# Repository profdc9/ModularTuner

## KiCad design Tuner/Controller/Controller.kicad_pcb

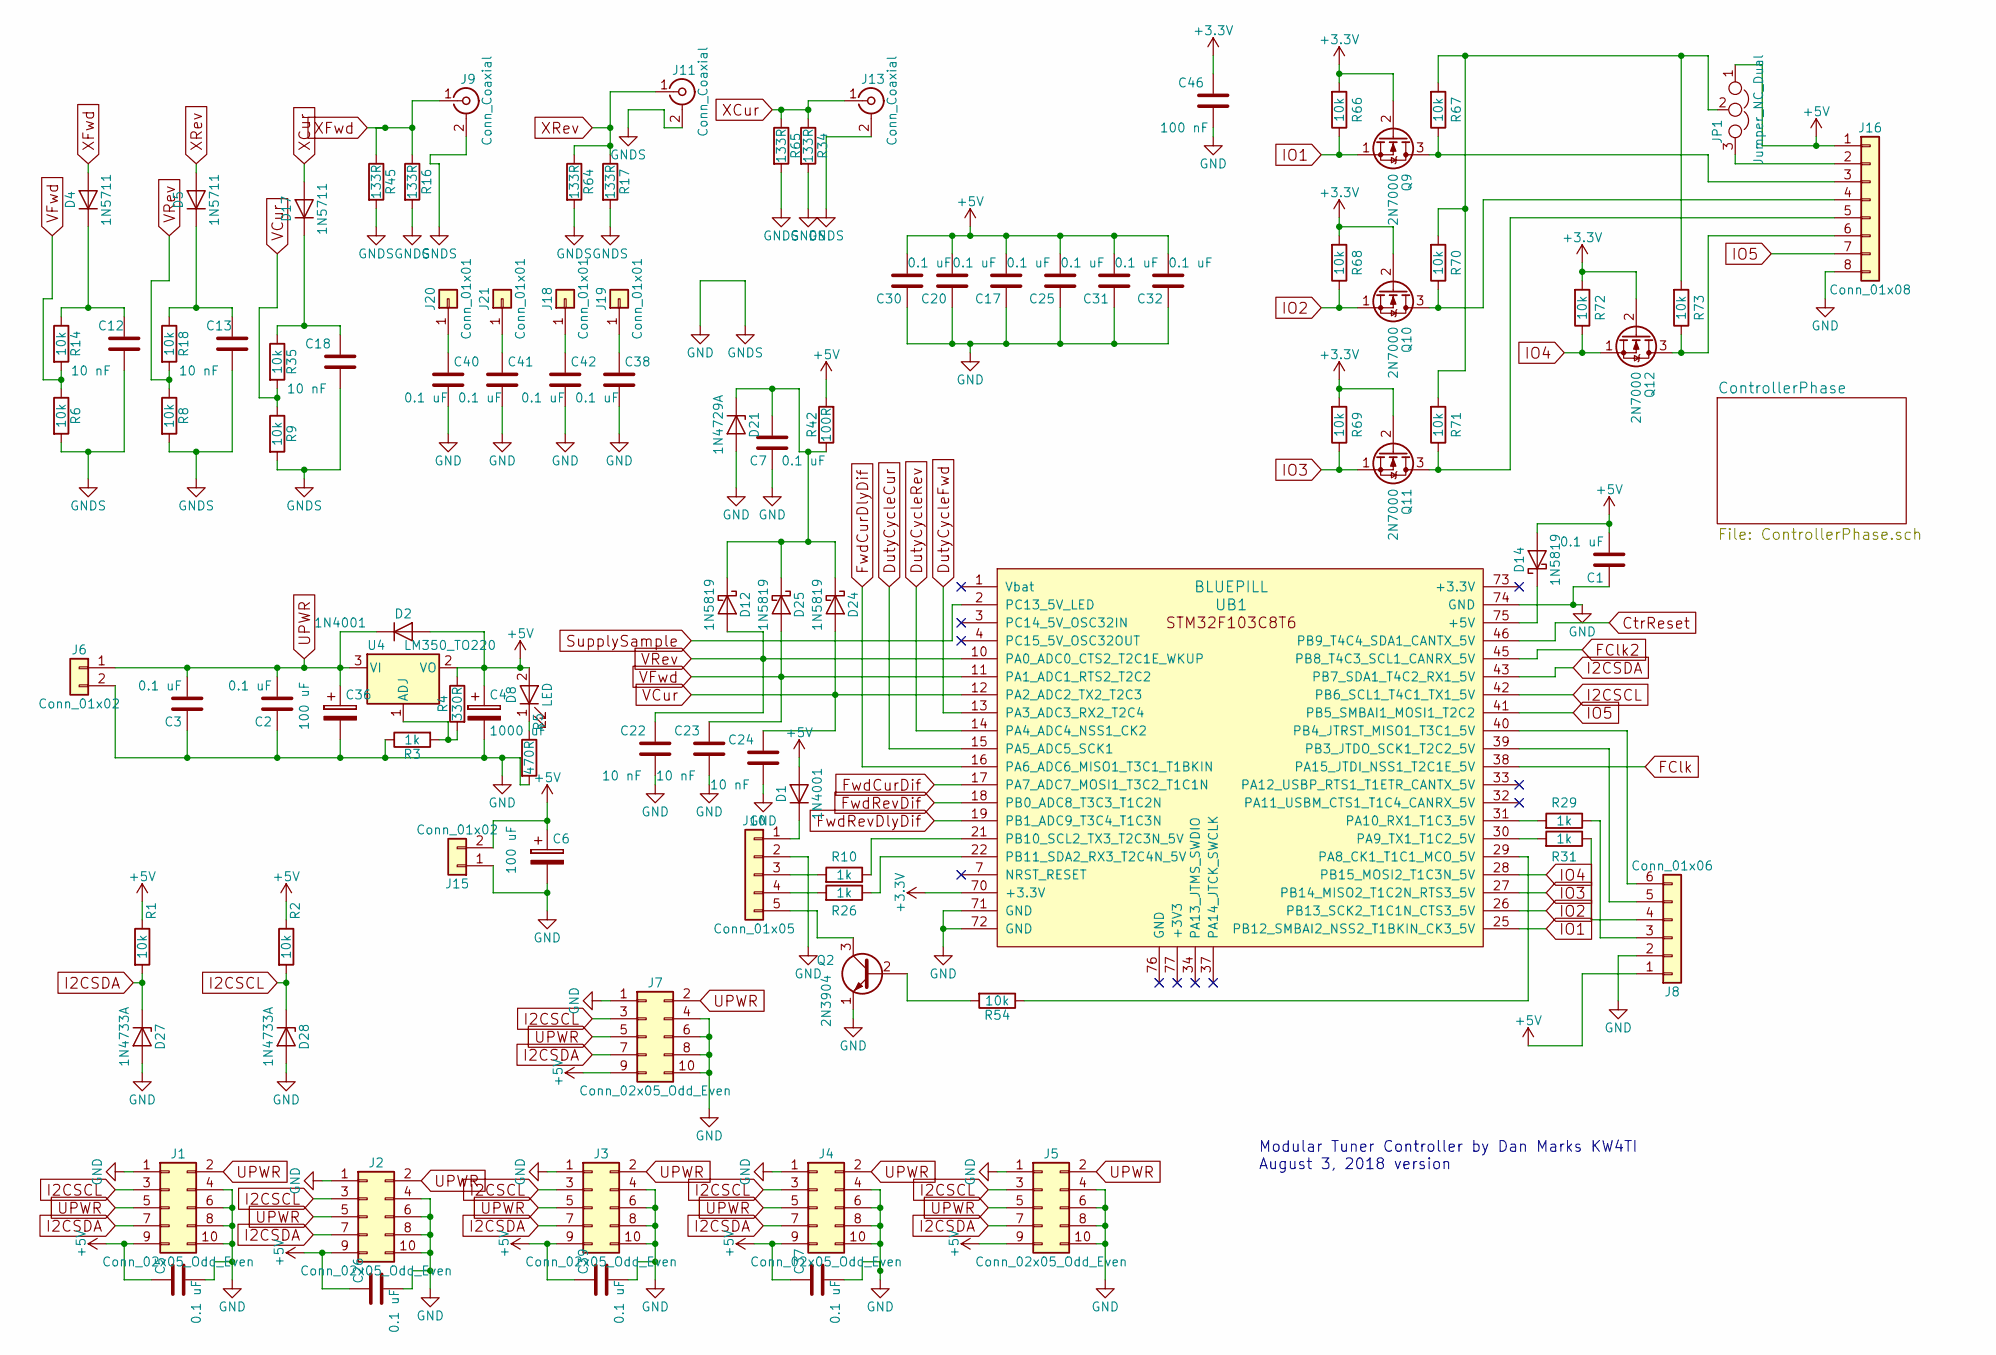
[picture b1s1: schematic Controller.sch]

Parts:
C1, C2, C7: 0.1 uF; C_Disc_D5.0mm_W2.5mm_P5.00mm
C3, C5, C17, C20, C25, C26, C30, C31, C32, C37, C38, C39, C40, C41, C42: 0.1 uF; C_Disc_D5.0mm_W2.5mm_P2.50mm
C4: 1000 uF; CP_Radial_D10.0mm_P5.00mm
C6, C36: 100 uF; CP_Radial_D5.0mm_P2.50mm
C12, C13, C18: 10 nF; C_Disc_D5.0mm_W2.5mm_P2.50mm
C22, C23, C24: 10 nF; C_Disc_D5.0mm_W2.5mm_P5.00mm
C46: 100 nF; C_Disc_D5.0mm_W2.5mm_P2.50mm
D1, D2: 1N4001; D_DO-41_SOD81_P7.62mm_Horizontal
D4, D5, D17: 1N5711; D_DO-35_SOD27_P7.62mm_Horizontal
D8: LED; LED_D3.0mm
D12, D14, D24, D25: 1N5819; D_DO-41_SOD81_P7.62mm_Horizontal
D21: 1N4729A; D_DO-41_SOD81_P7.62mm_Horizontal
D27, D28: 1N4733A; D_DO-41_SOD81_P7.62mm_Horizontal
J1, J2, J3, J4, J5, J7: Conn_02x05_Odd_Even; Pin_Header_Straight_2x05_Pitch2.54mm
J6, J15: Conn_01x02; TerminalBlock_bornier-2_P5.08mm
J8: Conn_01x06; Pin_Header_Straight_1x06_Pitch2.54mm
J9, J11, J13: Conn_Coaxial; bnc_90_1-1337543-0_pad_combo
J10: Conn_01x05; Pin_Header_Straight_1x05_Pitch2.54mm
J16: Conn_01x08; Pin_Header_Straight_1x08_Pitch2.54mm
J18, J19, J20, J21: Conn_01x01; 1pin
JP1: Jumper_NC_Dual; Pin_Header_Straight_1x03_Pitch2.54mm
Q2: 2N3904; TO-92_Molded_Narrow
Q9, Q10, Q11, Q12: 2N7000; TO-92_Molded_Narrow
R1, R2, R6, R8, R9, R14, R18, R35, R54, R66, R67, R68, R69, R70, R71, R72, R73: 10k; R_Axial_DIN0207_L6.3mm_D2.5mm_P7.62mm_Horizontal
R3, R10, R26, R29, R31: 1k; R_Axial_DIN0207_L6.3mm_D2.5mm_P7.62mm_Horizontal
R4: 330R; R_Axial_DIN0207_L6.3mm_D2.5mm_P7.62mm_Horizontal
R5: 470R; R_Axial_DIN0207_L6.3mm_D2.5mm_P7.62mm_Horizontal
R16, R17, R34, R45, R64, R65: 133R; R_Axial_DIN0309_L9.0mm_D3.2mm_P12.70mm_Horizontal
R42: 100R; R_Axial_DIN0207_L6.3mm_D2.5mm_P7.62mm_Horizontal
U4: LM350_TO220; TO-220-3_Vertical
UB1: BLUEPILL

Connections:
+3V3: C46.1, Q9.2 (G), Q10.2 (G), Q11.2 (G), Q12.2 (G), R66.2, R68.2, R69.2, R72.2, UB1.70 (+3.3V)
CtrReset: UB1.46 (PB9_T4C4_SDA1_CANTX_5V); also elsewhere on the board
DutyCycleCur: UB1.15 (PA5_ADC5_SCK1); also elsewhere on the board
DutyCycleFwd: UB1.13 (PA3_ADC3_RX2_T2C4); also elsewhere on the board
DutyCycleRev: UB1.14 (PA4_ADC4_NSS1_CK2); also elsewhere on the board
FClk2: UB1.45 (PB8_T4C3_SCL1_CANRX_5V); also elsewhere on the board
FwdCurDif: UB1.17 (PA7_ADC7_MOSI1_T3C2_T1C1N); also elsewhere on the board
FwdCurDlyDif: UB1.16 (PA6_ADC6_MISO1_T3C1_T1BKIN); also elsewhere on the board
FwdRevDif: UB1.18 (PB0_ADC8_T3C3_T1C2N); also elsewhere on the board
FwdRevDlyDif: UB1.19 (PB1_ADC9_T3C4_T1C3N); also elsewhere on the board
GND: C1.1, C2.1, C3.1, C4.2, C5.2, C6.2, C7.1, C12.2, C13.2, C17.1, C18.2, C20.1, C22.2, C23.2, C24.2, C25.1, C26.2, C30.1, C31.1, C32.1, C36.2, C37.2, C38.2, C39.2, C40.2, C41.2, C42.2, C46.2, D21.2 (A), D27.2 (A), D28.2 (A), J1.1, J1.4, J1.6, J1.8, J1.10, J2.1, J2.4, J2.6, J2.8, J2.10, J3.1, J3.4, J3.6, J3.8, J3.10, J4.1, J4.4, J4.6, J4.8, J4.10, J5.1, J5.4, J5.6, J5.8, J5.10, J6.2, J7.1, J7.4, J7.6, J7.8, J7.10, J8.2, J9.2 (Ext), J10.2, J11.2 (Ext), J13.2 (Ext), J15.1, J16.8, Q2.1 (E), R3.1, R5.2, R6.2, R8.2, R9.2, R16.2, R17.2, R34.2, R45.2, R64.2, R65.2, UB1.71 (GND), UB1.72 (GND), UB1.74 (GND); also elsewhere on the board
I2CSCL: D28.1 (K), J1.3, J2.3, J3.3, J4.3, J5.3, J7.3, R2.2, UB1.42 (PB6_SCL1_T4C1_TX1_5V)
I2CSDA: D27.1 (K), J1.7, J2.7, J3.7, J4.7, J5.7, J7.7, R1.2, UB1.43 (PB7_SDA1_T4C2_RX1_5V)
IO1: Q9.1 (S), R66.1, UB1.25 (PB12_SMBAI2_NSS2_T1BKIN_CK3_5V)
IO2: Q10.1 (S), R68.1, UB1.26 (PB13_SCK2_T1C1N_CTS3_5V)
IO3: Q11.1 (S), R69.1, UB1.27 (PB14_MISO2_T1C2N_RTS3_5V)
IO4: Q12.1 (S), R72.1, UB1.28 (PB15_MOSI2_T1C3N_5V)
IO5: J16.7, UB1.41 (PB5_SMBAI1_MOSI1_T2C2)
unnamed: C7.2, D12.1 (K), D21.1 (K), D24.1 (K), D25.1 (K), R42.1
unnamed: C12.1, D4.1 (K), R14.1
unnamed: C13.1, D5.1 (K), R18.1
unnamed: C18.1, D17.1 (K), R35.1
unnamed: C38.1, J19.1
unnamed: C40.1, J20.1
unnamed: C41.1, J21.1
unnamed: C42.1, J18.1
unnamed: D1.1 (K), J10.1
unnamed: D8.1 (K), R5.1
unnamed: D14.1 (K), UB1.75 (+5V)
unnamed: J8.3, R29.1
unnamed: J8.4, R31.1
unnamed: J8.5, UB1.39 (PB3_JTDO_SCK1_T2C2_5V)
unnamed: J8.6, UB1.40 (PB4_JTRST_MISO1_T3C1_5V)
unnamed: J10.3, R10.2
unnamed: J10.4, R26.2
unnamed: J10.5, Q2.3 (C)
unnamed: J16.2, JP1.3
unnamed: J16.3, Q9.3 (D), R67.1
unnamed: J16.4, Q10.3 (D), R70.1
unnamed: J16.5, Q11.3 (D), R71.1
unnamed: J16.6, Q12.3 (D), R73.1
unnamed: JP1.2, R67.2, R70.2, R71.2, R73.2
unnamed: Q2.2 (B), R54.2
unnamed: R3.2, R4.2, U4.1 (ADJ)
unnamed: R10.1, UB1.21 (PB10_SCL2_TX3_T2C3N_5V)
unnamed: R26.1, UB1.22 (PB11_SDA2_RX3_T2C4N_5V)
unnamed: R29.2, UB1.31 (PA10_RX1_T1C3_5V)
unnamed: R31.2, UB1.30 (PA9_TX1_T1C2_5V)
unnamed: R54.1, UB1.29 (PA8_CK1_T1C1_MCO_5V)
SupplySample: UB1.2 (PC13_5V_LED); also elsewhere on the board
UPWR: C2.2, C3.2, C36.1, D2.1 (K), J1.2, J1.5, J2.2, J2.5, J3.2, J3.5, J4.2, J4.5, J5.2, J5.5, J6.1, J7.2, J7.5, U4.3 (VI)
VCur: C24.1, D24.2 (A), R9.1, R35.2, UB1.12 (PA2_ADC2_TX2_T2C3)
VFwd: C23.1, D25.2 (A), R6.1, R14.2, UB1.11 (PA1_ADC1_RTS2_T2C2)
VRev: C22.1, D12.2 (A), R8.1, R18.2, UB1.10 (PA0_ADC0_CTS2_T2C1E_WKUP)
XCur: D17.2 (A), J13.1 (In), R34.1, R65.1; also elsewhere on the board
XFwd: D4.2 (A), J9.1 (In), R16.1, R45.1; also elsewhere on the board
XRev: D5.2 (A), J11.1 (In), R17.1, R64.1; also elsewhere on the board

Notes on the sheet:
Modular Tuner Controller by Dan Marks KW4TI August 3, 2018 version

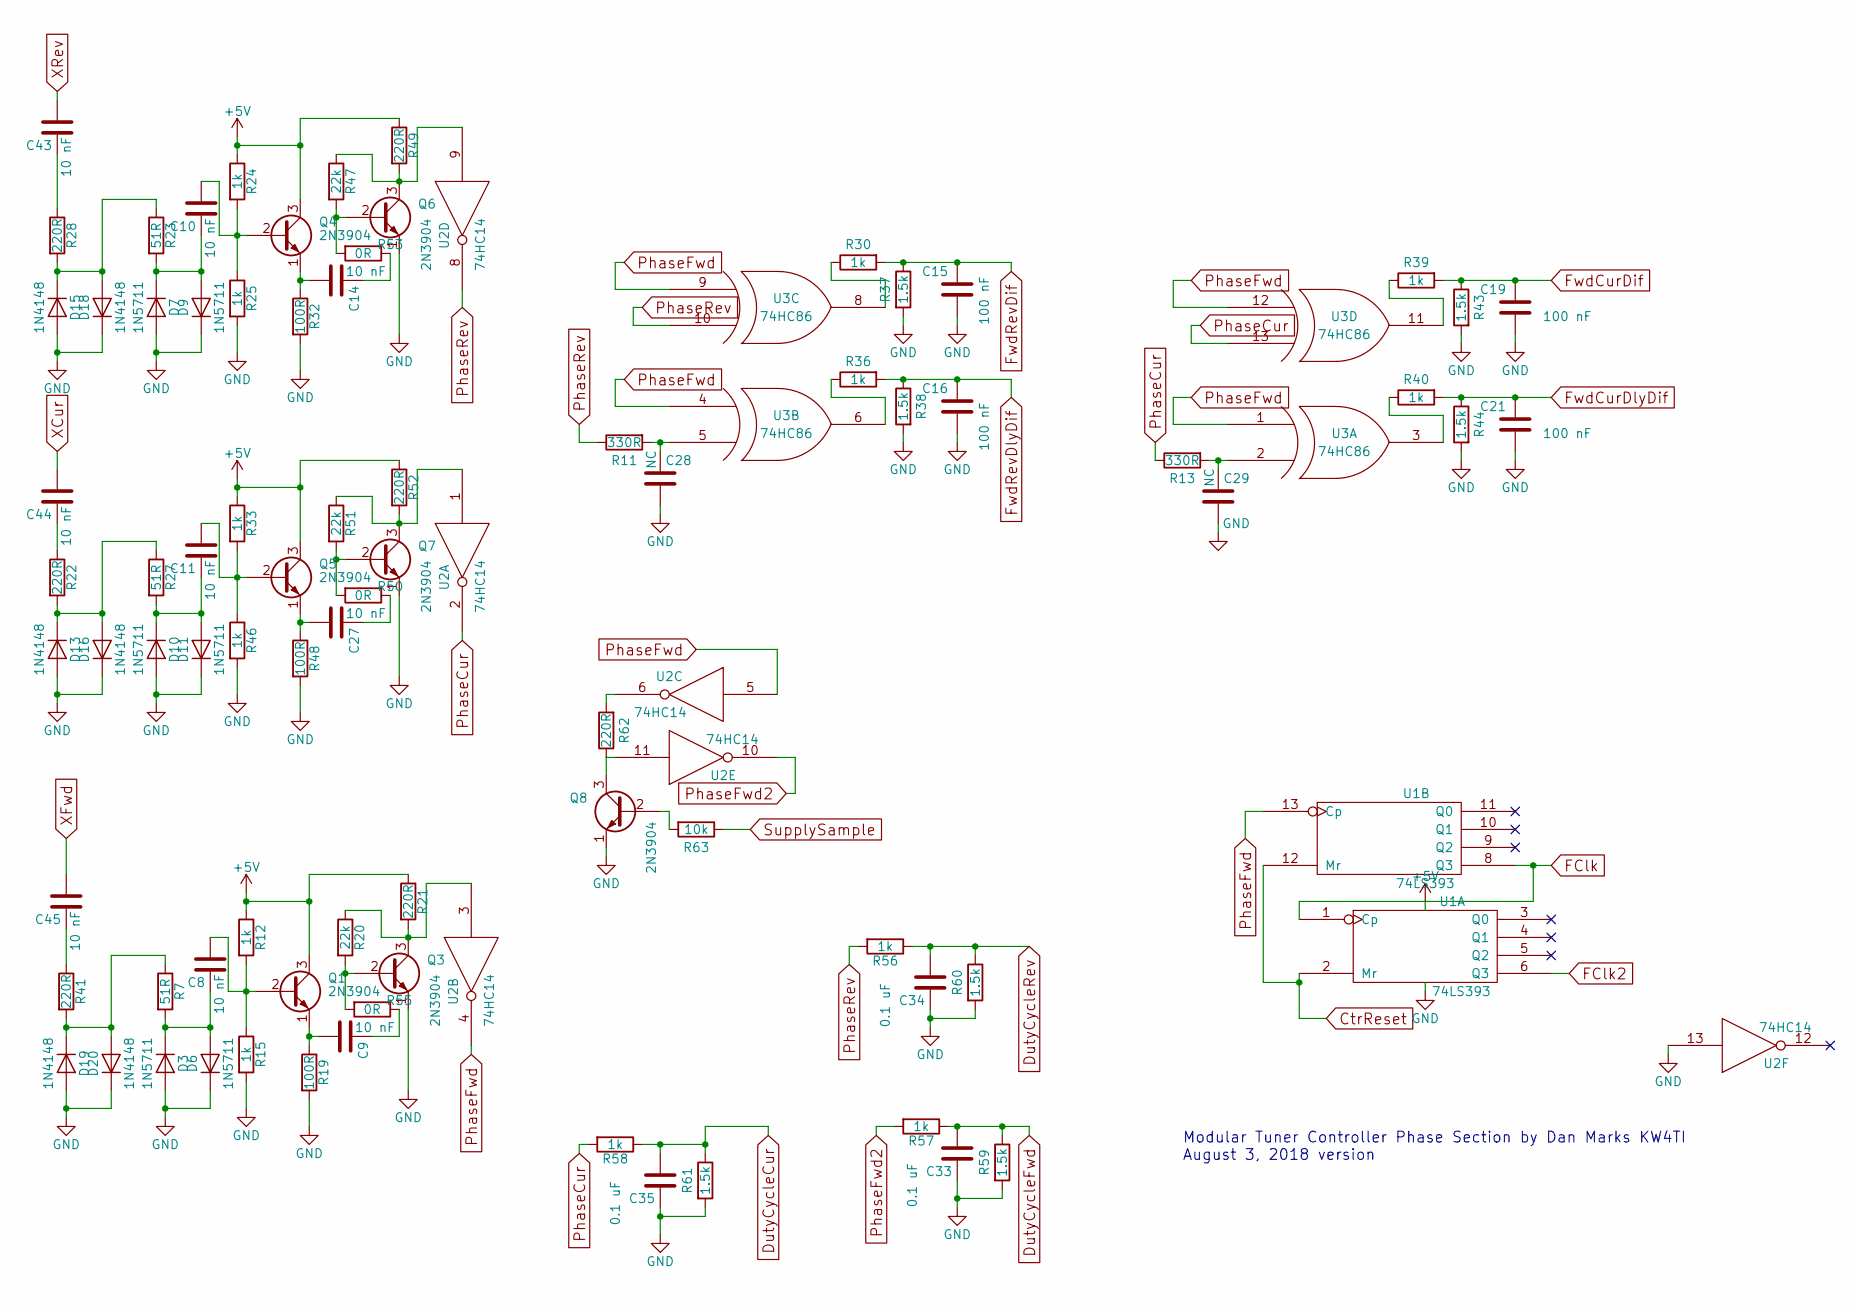
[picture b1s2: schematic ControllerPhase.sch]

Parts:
C8, C9, C10, C11, C14, C27, C43, C44, C45: 10 nF; C_Disc_D5.0mm_W2.5mm_P2.50mm
C15, C16, C19, C21: 100 nF; C_Disc_D5.0mm_W2.5mm_P5.00mm
C28, C29: NC; C_Disc_D5.0mm_W2.5mm_P5.00mm
C33, C34, C35: 0.1 uF; C_Disc_D5.0mm_W2.5mm_P5.00mm
D3, D6, D7, D9, D10, D11: 1N5711; D_DO-35_SOD27_P7.62mm_Horizontal
D13, D15, D16, D18, D19, D20: 1N4148; D_DO-35_SOD27_P7.62mm_Horizontal
Q1, Q3, Q4, Q5, Q6, Q7, Q8: 2N3904; TO-92_Molded_Narrow
R7, R23, R27: 51R; R_Axial_DIN0207_L6.3mm_D2.5mm_P7.62mm_Horizontal
R11, R13: 330R; R_Axial_DIN0207_L6.3mm_D2.5mm_P7.62mm_Horizontal
R12, R15, R24, R25, R30, R33, R36, R39, R40, R46, R56, R57, R58: 1k; R_Axial_DIN0207_L6.3mm_D2.5mm_P7.62mm_Horizontal
R19, R32, R48: 100R; R_Axial_DIN0207_L6.3mm_D2.5mm_P7.62mm_Horizontal
R20, R47, R51: 22k; R_Axial_DIN0207_L6.3mm_D2.5mm_P7.62mm_Horizontal
R21, R22, R28, R41, R49, R52, R62: 220R; R_Axial_DIN0207_L6.3mm_D2.5mm_P7.62mm_Horizontal
R37, R38, R43, R44, R59, R60, R61: 1.5k; R_Axial_DIN0207_L6.3mm_D2.5mm_P7.62mm_Horizontal
R50, R53, R55: 0R; R_Axial_DIN0207_L6.3mm_D2.5mm_P7.62mm_Horizontal
R63: 10k; R_Axial_DIN0207_L6.3mm_D2.5mm_P7.62mm_Horizontal
U1: 74LS393; DIP-14_W7.62mm_Socket
U2: 74HC14; DIP-14_W7.62mm_Socket
U3: 74HC86; DIP-14_W7.62mm_Socket

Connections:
CtrReset: U1.2 (Mr), U1.12 (Mr); also elsewhere on the board
DutyCycleCur: C35.2, R58.1, R61.1; also elsewhere on the board
DutyCycleFwd: C33.2, R57.1, R59.1; also elsewhere on the board
DutyCycleRev: C34.2, R56.1, R60.1; also elsewhere on the board
FClk2: U1.6 (Q3); also elsewhere on the board
FwdCurDif: C19.1, R39.2, R43.1; also elsewhere on the board
FwdCurDlyDif: C21.1, R40.2, R44.1; also elsewhere on the board
FwdRevDif: C15.1, R30.2, R37.1; also elsewhere on the board
FwdRevDlyDif: C16.1, R36.2, R38.1; also elsewhere on the board
GND: C15.2, C16.2, C19.2, C21.2, C28.2, C29.2, C33.1, C34.1, C35.1, D3.2 (A), D6.1 (K), D7.2 (A), D9.1 (K), D10.2 (A), D11.1 (K), D13.2 (A), D15.2 (A), D16.1 (K), D18.1 (K), D19.2 (A), D20.1 (K), Q3.1 (E), Q6.1 (E), Q7.1 (E), Q8.1 (E), R15.2, R19.2, R25.2, R32.2, R37.2, R38.2, R43.2, R44.2, R46.2, R48.2, R59.2, R60.2, R61.2, U1.7 (GND), U2.7 (GND), U2.13, U3.7 (GND); also elsewhere on the board
unnamed: C8.1, D3.1 (K), D6.2 (A), R7.2
unnamed: C8.2, Q1.2 (B), R12.2, R15.1
unnamed: C9.1, R55.1
unnamed: C9.2, Q1.1 (E), R19.1
unnamed: C10.1, D7.1 (K), D9.2 (A), R23.2
unnamed: C10.2, Q4.2 (B), R24.2, R25.1
unnamed: C11.1, D10.1 (K), D11.2 (A), R27.2
unnamed: C11.2, Q5.2 (B), R33.2, R46.1
unnamed: C14.1, R53.1
unnamed: C14.2, Q4.1 (E), R32.1
unnamed: C27.1, R50.1
unnamed: C27.2, Q5.1 (E), R48.1
unnamed: C28.1, R11.2, U3.5 (IN2)
unnamed: C29.1, R13.2, U3.2 (IN2)
unnamed: C43.1, R28.1
unnamed: C44.1, R22.1
unnamed: C45.1, R41.1
unnamed: D13.1 (K), D16.2 (A), R22.2, R27.1
unnamed: D15.1 (K), D18.2 (A), R23.1, R28.2
unnamed: D19.1 (K), D20.2 (A), R7.1, R41.2
unnamed: Q3.2 (B), R20.2, R55.2
unnamed: Q3.3 (C), R20.1, R21.2, U2.3
unnamed: Q6.2 (B), R47.2, R53.2
unnamed: Q6.3 (C), R47.1, R49.2, U2.9
unnamed: Q7.2 (B), R50.2, R51.2
unnamed: Q7.3 (C), R51.1, R52.2, U2.1
unnamed: Q8.2 (B), R63.2
unnamed: Q8.3 (C), R62.1, U2.11
unnamed: R30.1, U3.8 (OUT)
unnamed: R36.1, U3.6 (OUT)
unnamed: R39.1, U3.11 (OUT)
unnamed: R40.1, U3.3 (OUT)
unnamed: R62.2, U2.6
PhaseCur: R13.1, R58.2, U2.2, U3.13 (IN2)
PhaseFwd: U1.13 (Cp), U2.4, U2.5, U3.1 (IN1), U3.4 (IN1), U3.9 (IN1), U3.12 (IN1)
PhaseFwd2: R57.2, U2.10
PhaseRev: R11.1, R56.2, U2.8, U3.10 (IN2)
SupplySample: R63.1; also elsewhere on the board
XCur: C44.2; also elsewhere on the board
XFwd: C45.2; also elsewhere on the board
XRev: C43.2; also elsewhere on the board

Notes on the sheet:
Modular Tuner Controller Phase Section by Dan Marks KW4TI August 3, 2018 version

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
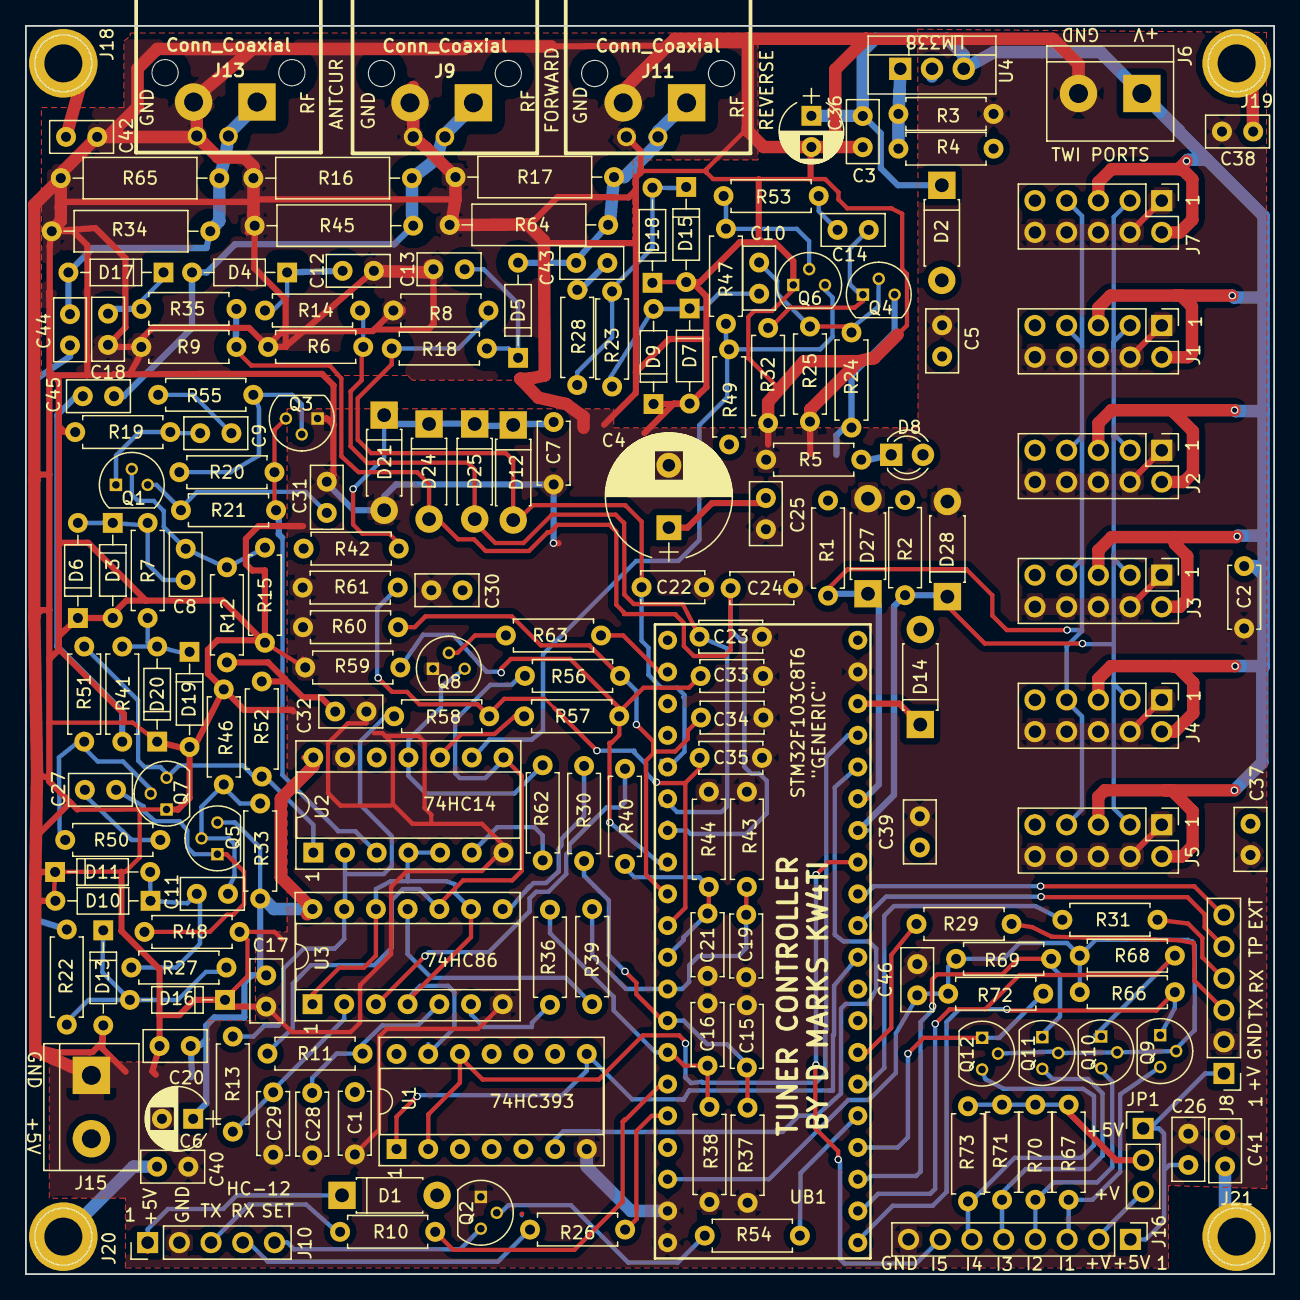
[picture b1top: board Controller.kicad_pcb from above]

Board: 2 copper layers, 100.0 x 100.0 mm, 180 parts (0 on the bottom side), 96 nets.

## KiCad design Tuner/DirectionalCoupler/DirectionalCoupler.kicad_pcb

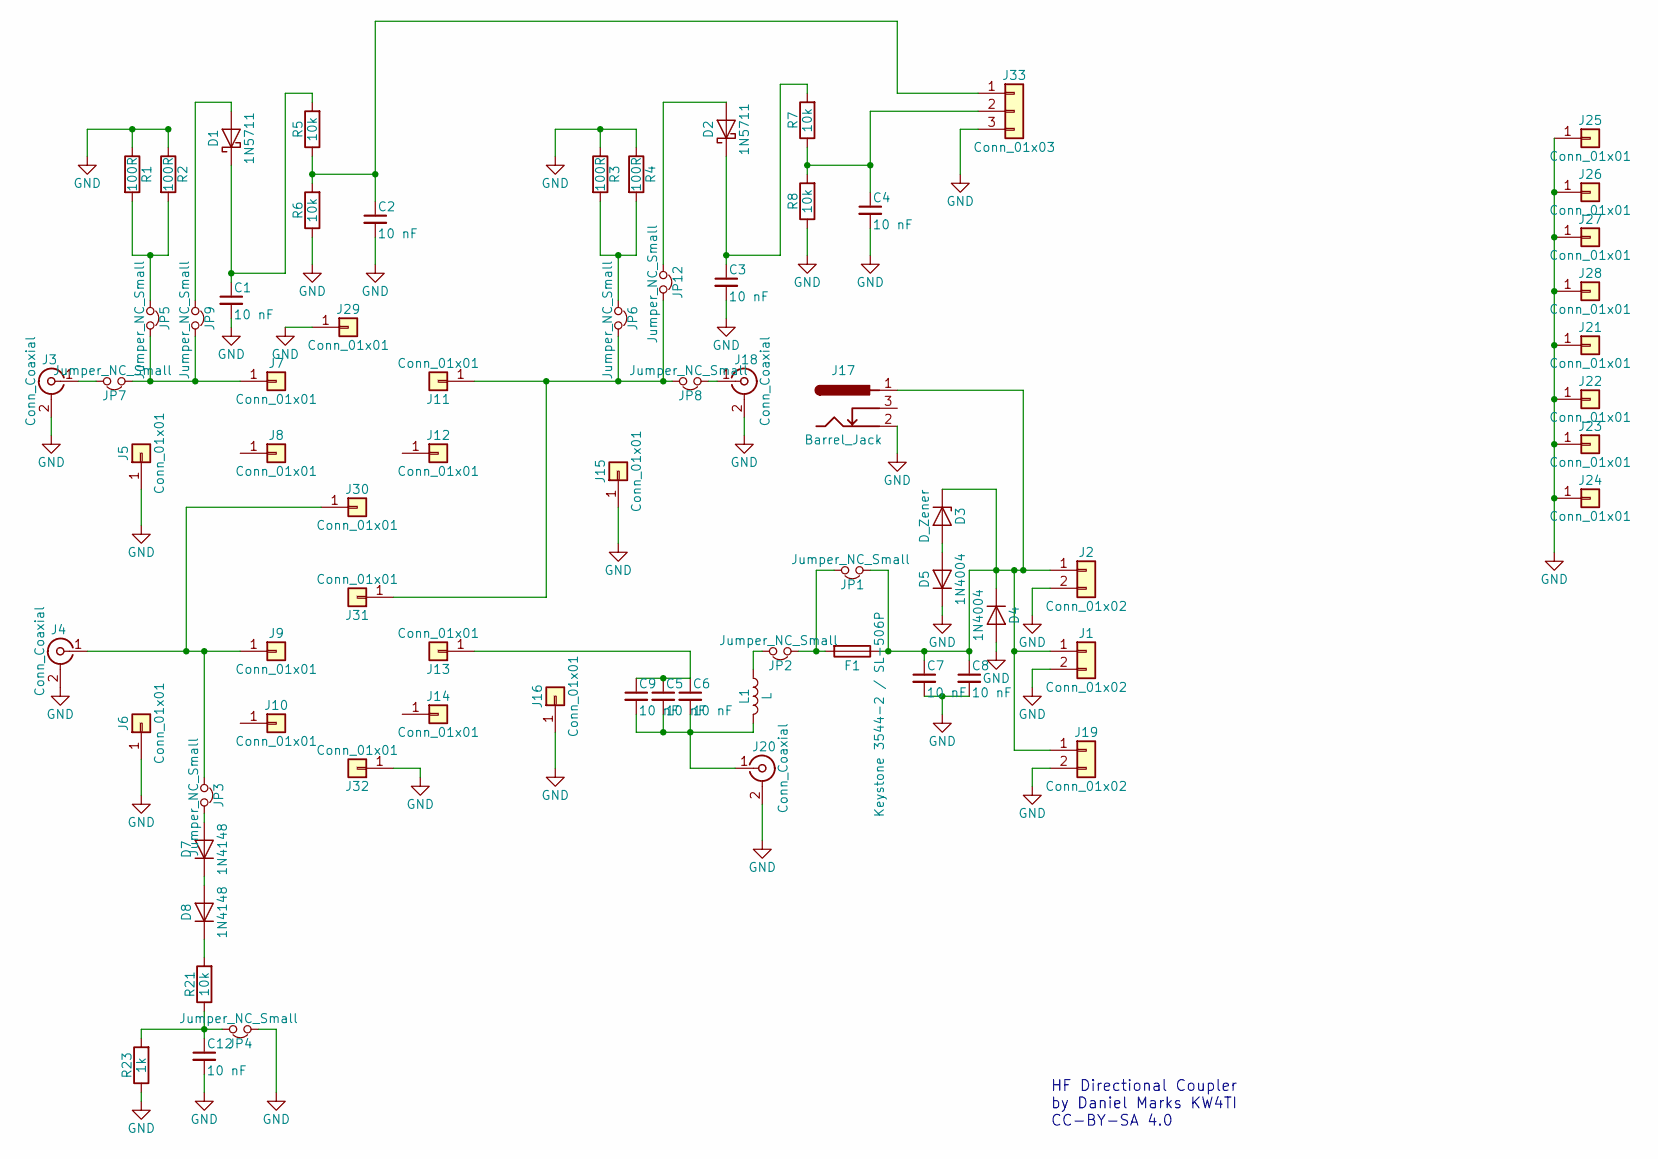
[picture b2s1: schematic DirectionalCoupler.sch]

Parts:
C1, C2, C3, C4, C5, C6, C7, C8, C9: 10 nF; C_Disc_D5.0mm_W2.5mm_P5.00mm
C12: 10 nF; C_Disc_D5.0mm_W2.5mm_P2.50mm
D1, D2: 1N5711; D_DO-35_SOD27_P7.62mm_Horizontal
D3: D_Zener; D_DO-41_SOD81_P10.16mm_Horizontal
D4, D5: 1N4004; D_DO-41_SOD81_P10.16mm_Horizontal
D7, D8: 1N4148; D_DO-35_SOD27_P7.62mm_Horizontal
F1: Keystone 3544-2 / SL-506P; SL506Pfuseholder
J1, J2, J19: Conn_01x02; TerminalBlock_bornier-2_P5.08mm
J3, J4, J18, J20: Conn_Coaxial; bnc_90_1-1337543-0_pad_combo
J5, J6, J7, J8, J9, J10, J11, J12, J13, J14, J15, J16, J21, J22, J23, J24, J25, J26, J27, J28, J29, J30, J31, J32: Conn_01x01; 1pin
J17: Barrel_Jack; BARREL_JACK
J33: Conn_01x03; Pin_Header_Straight_1x03_Pitch2.54mm
JP1, JP2, JP3, JP4, JP5, JP6, JP7, JP8, JP9, JP12: Jumper_NC_Small; Pin_Header_Straight_1x02_Pitch2.54mm
L1: L; BigRFChokeInductor
R1, R2, R3, R4: 100R; R_Axial_DIN0309_L9.0mm_D3.2mm_P12.70mm_Horizontal
R5, R6, R7, R8, R21: 10k; R_Axial_DIN0207_L6.3mm_D2.5mm_P7.62mm_Horizontal
R23: 1k; R_Axial_DIN0207_L6.3mm_D2.5mm_P7.62mm_Horizontal

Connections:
GND: C1.2, C2.2, C3.2, C4.2, C7.2, C8.2, C12.2, D4.2 (A), D5.1 (K), J1.2, J2.2, J3.2 (Ext), J4.2 (Ext), J5.1, J6.1, J15.1, J16.1, J17.2, J18.2 (Ext), J19.2, J20.2 (Ext), J21.1, J22.1, J23.1, J24.1, J25.1, J26.1, J27.1, J28.1, J29.1, J32.1, J33.3, JP4.1, R1.1, R2.1, R3.1, R4.1, R6.1, R8.1, R23.1
unnamed: C1.1, D1.1 (K), R5.2
unnamed: C2.1, J33.1, R5.1, R6.2
unnamed: C3.1, D2.1 (K), R7.2
unnamed: C4.1, J33.2, R7.1, R8.2
unnamed: C5.1, C6.1, C9.1, J13.1
unnamed: C5.2, C6.2, C9.2, J20.1 (In), L1.2
unnamed: C7.1, C8.1, D3.1 (K), D4.1 (K), F1.1, J1.1, J2.1, J17.1, J19.1, JP1.1
unnamed: C12.1, JP4.2, R21.1, R23.2
unnamed: D1.2 (A), JP9.1
unnamed: D2.2 (A), JP12.1
unnamed: D3.2 (A), D5.2 (A)
unnamed: D7.1 (K), D8.2 (A)
unnamed: D7.2 (A), JP3.2
unnamed: D8.1 (K), R21.2
unnamed: F1.2, JP1.2, JP2.1
unnamed: J3.1 (In), JP7.2
unnamed: J7.1, JP5.2, JP7.1, JP9.2
unnamed: J11.1, J31.1, JP6.2, JP8.2, JP12.2
unnamed: J18.1 (In), JP8.1
unnamed: J4.1 (In), J9.1, J30.1, JP3.1
unnamed: JP2.2, L1.1
unnamed: JP5.1, R1.2, R2.2
unnamed: JP6.1, R3.2, R4.2

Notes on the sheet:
HF Directional Coupler by Daniel Marks KW4TI CC-BY-SA 4.0

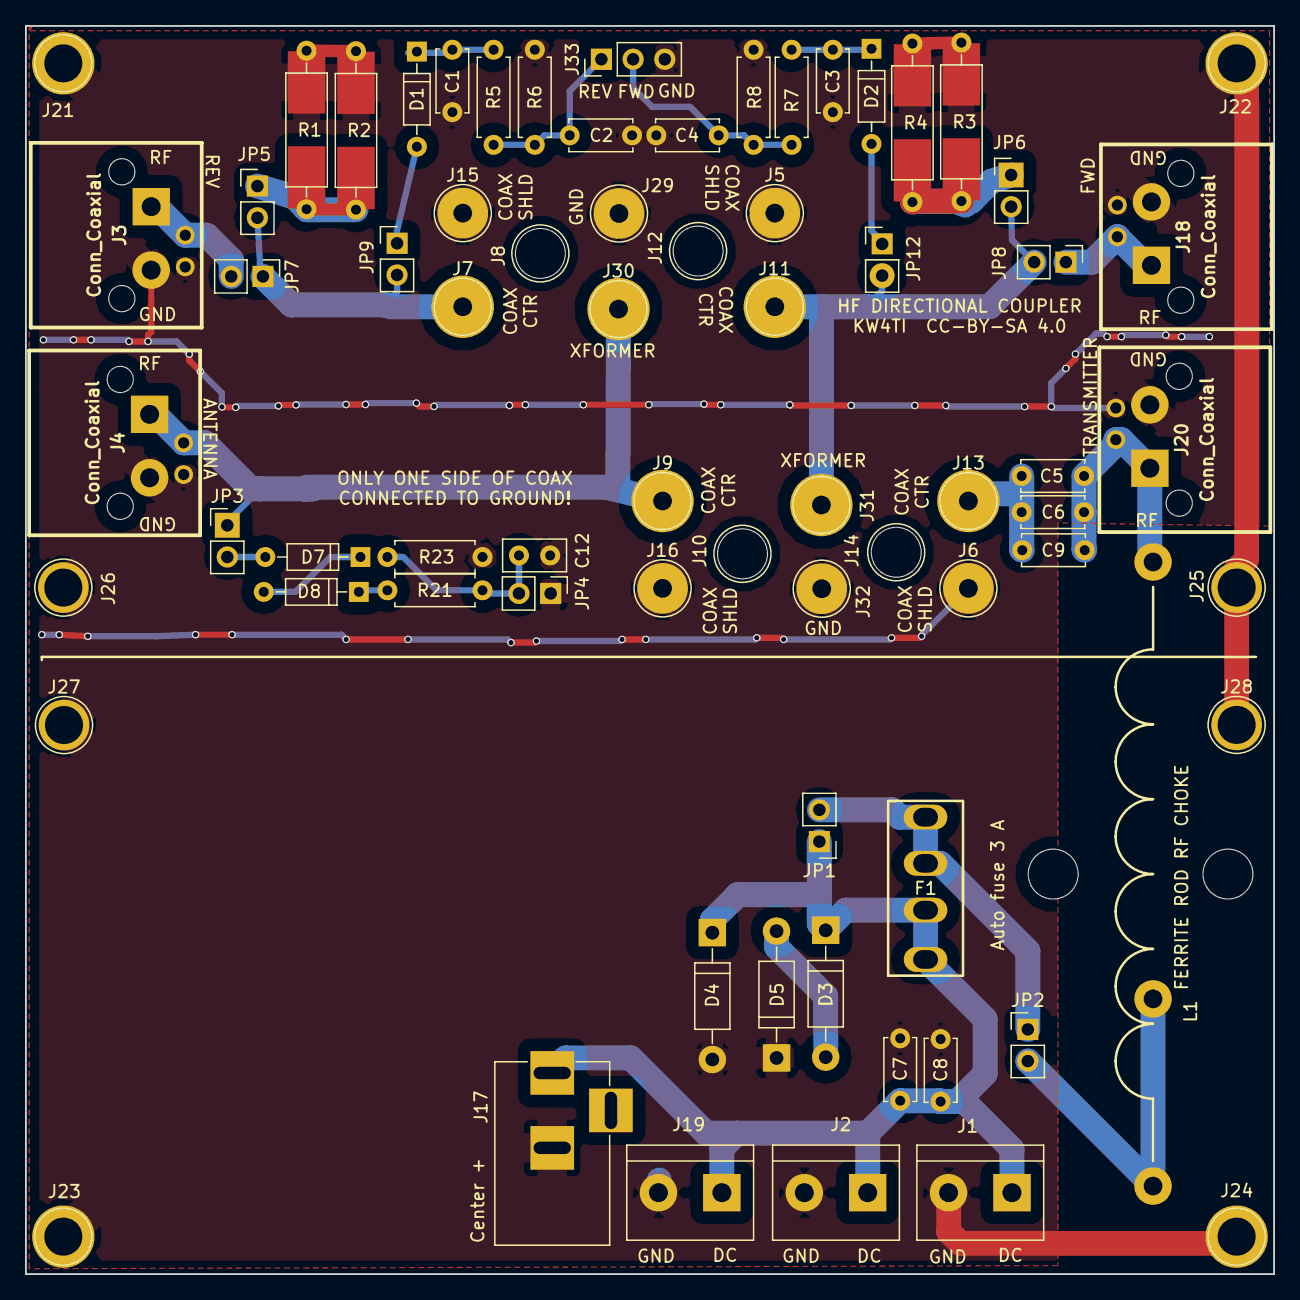
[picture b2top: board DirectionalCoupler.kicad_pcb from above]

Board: 2 copper layers, 100.0 x 100.0 mm, 72 parts (0 on the bottom side), 24 nets.

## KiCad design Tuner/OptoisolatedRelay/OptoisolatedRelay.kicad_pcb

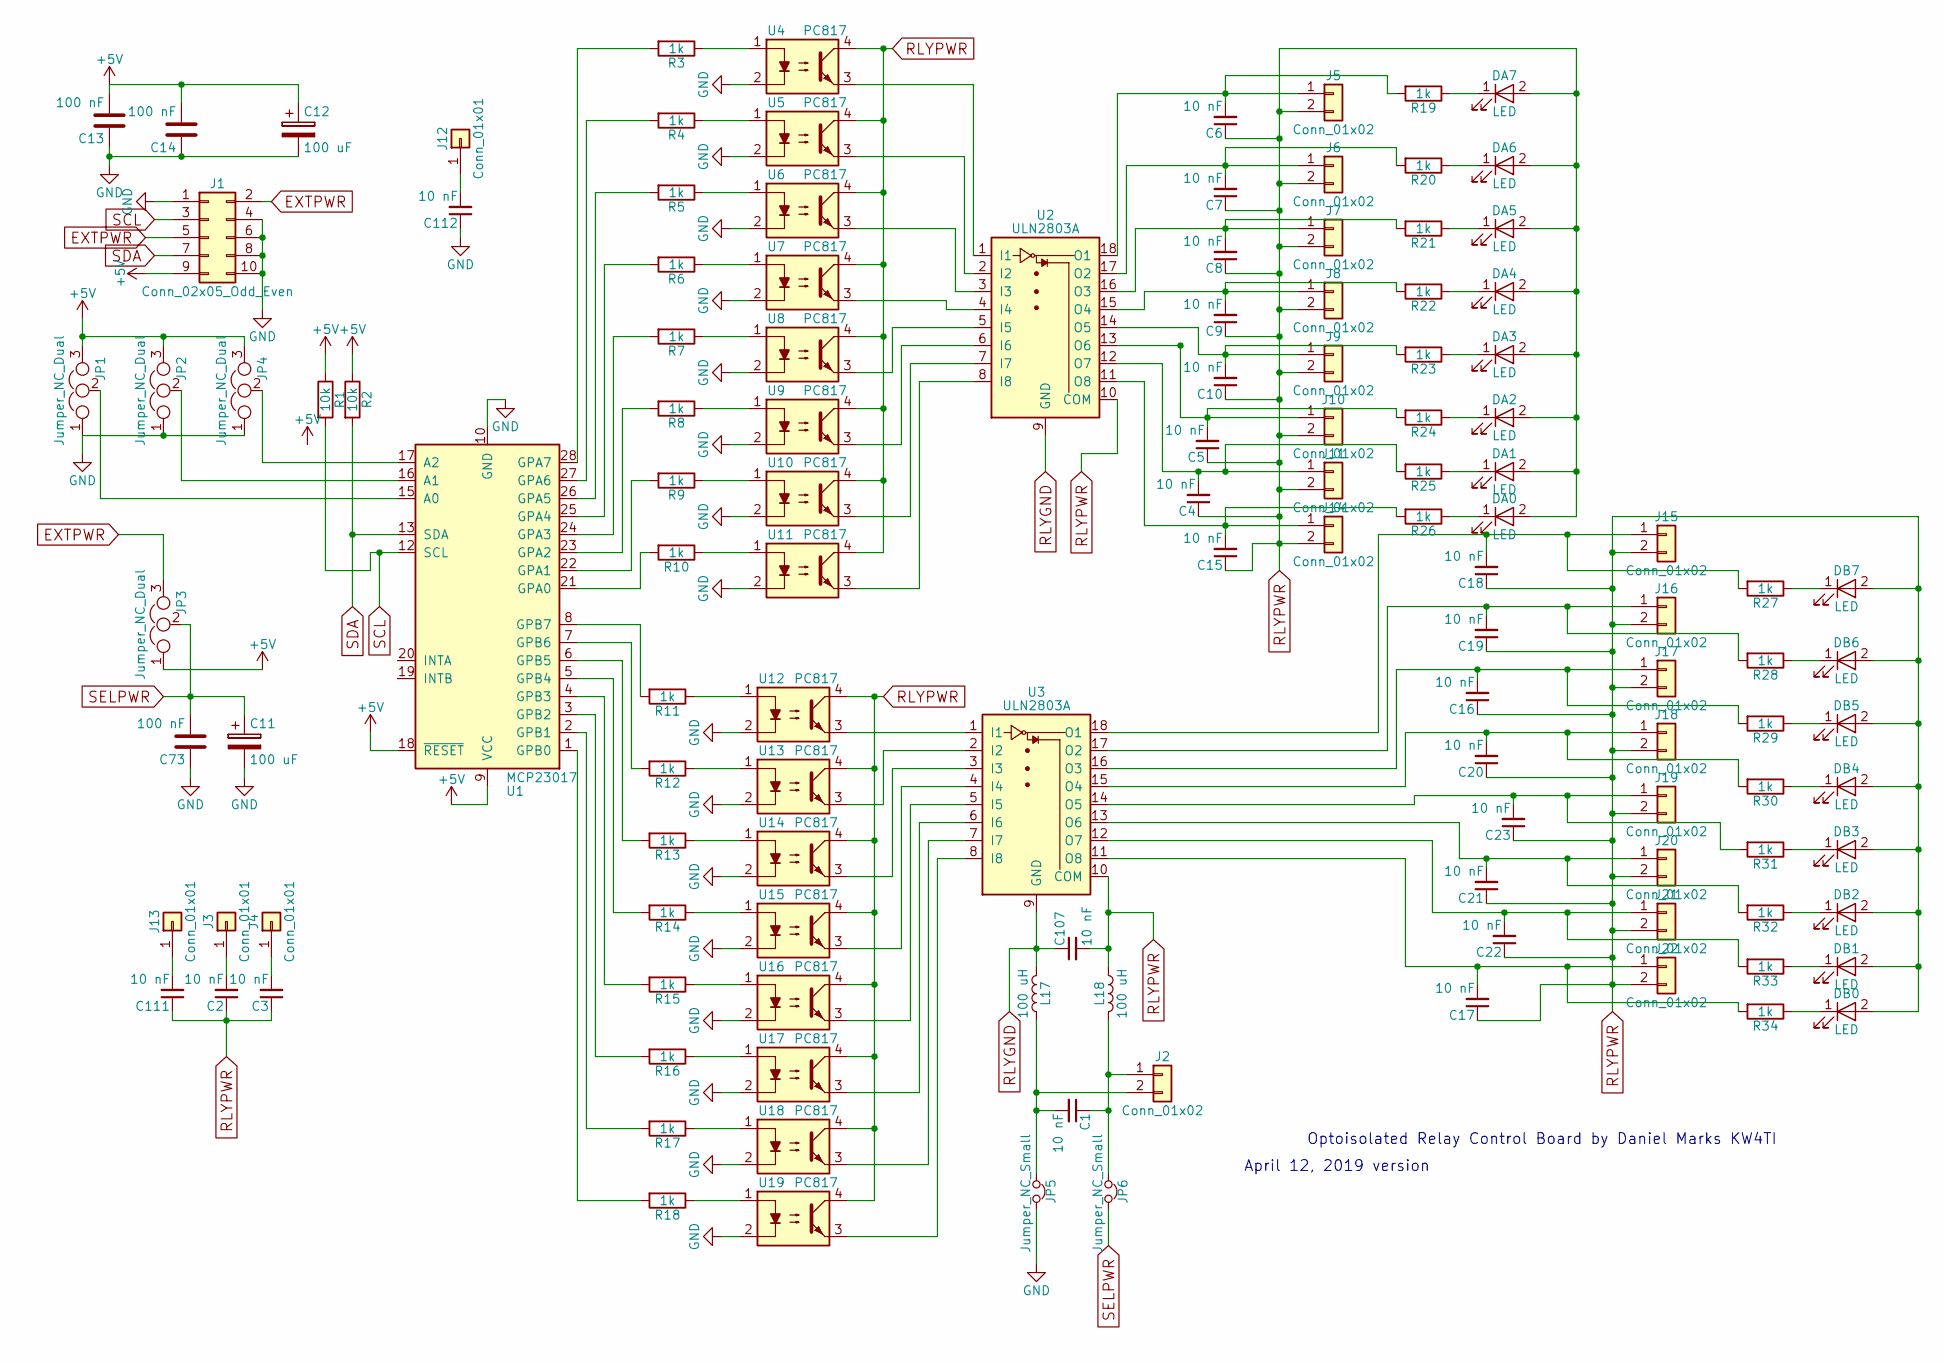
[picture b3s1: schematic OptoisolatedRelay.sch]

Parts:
C1, C107, C112: 10 nF; C_Disc_D5.0mm_W2.5mm_P2.50mm
C2, C3, C4, C5, C6, C7, C8, C9, C10, C15, C16, C17, C18, C19, C20, C21, C22, C23, C111: 10 nF; C_Disc_D5.0mm_W2.5mm_P5.00mm
C11, C12: 100 uF; CP_Radial_D8.0mm_P5.00mm
C13, C14, C73: 100 nF; C_Disc_D5.0mm_W2.5mm_P2.50mm
DA0, DA1, DA2, DA3, DA4, DA5, DA6, DA7: LED; LED_D3.0mm
DB0, DB1, DB2, DB3, DB4, DB5, DB6, DB7: LED; LED_D3.0mm
J1: Conn_02x05_Odd_Even; Pin_Header_Straight_2x05_Pitch2.54mm
J2, J5, J6, J7, J8, J9, J10, J11, J14, J15, J16, J17, J18, J19, J20, J21, J22: Conn_01x02; TerminalBlock_bornier-2_P5.08mm
J3, J4, J12, J13: Conn_01x01; 1pin
JP1, JP2, JP3, JP4: Jumper_NC_Dual; Pin_Header_Straight_1x03_Pitch2.54mm
JP5, JP6: Jumper_NC_Small; Pin_Header_Straight_1x02_Pitch2.54mm
L17, L18: 100 uH; L_Axial_L5.3mm_D2.2mm_P7.62mm_Horizontal_Vishay_IM-1
R1, R2: 10k; R_Axial_DIN0207_L6.3mm_D2.5mm_P7.62mm_Horizontal
R3, R4, R5, R6, R7, R8, R9, R10, R11, R12, R13, R14, R15, R16, R17, R18, R19, R20, R21, R22, R23, R24, R25, R26, R27, R28, R29, R30, R31, R32, R33, R34: 1k; R_Axial_DIN0207_L6.3mm_D2.5mm_P7.62mm_Horizontal
U1: MCP23017; DIP-28_W7.62mm_Socket
U2, U3: ULN2803A; DIP-18_W7.62mm_Socket
U4, U5, U6, U7, U8, U9, U10, U11, U12, U13, U14, U15, U16, U17, U18, U19: PC817; DIP-4_W7.62mm

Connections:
+5V: C12.1, C13.2, C14.2, J1.9, JP1.3, JP2.3, JP3.1, JP4.3, R1.1, R2.1, U1.9 (VCC), U1.18 (~RESET)
EXTPWR: J1.2, J1.5, JP3.3
GND: C11.2, C12.2, C13.1, C14.1, C73.1, C112.1, J1.1, J1.4, J1.6, J1.8, J1.10, JP1.1, JP2.1, JP4.1, JP5.2, U1.10 (GND), U4.2, U5.2, U6.2, U7.2, U8.2, U9.2, U10.2, U11.2, U12.2, U13.2, U14.2, U15.2, U16.2, U17.2, U18.2, U19.2
unnamed: C1.1, J2.1, JP6.1, L18.2
unnamed: C1.2, J2.2, JP5.1, L17.1
unnamed: C2.2, J3.1
unnamed: C3.2, J4.1
unnamed: C4.2, J11.1, R25.2, U2.12 (O7)
unnamed: C5.2, J10.1, R24.2, U2.13 (O6)
unnamed: C6.2, J5.1, R19.2, U2.18 (O1)
unnamed: C7.2, J6.1, R20.2, U2.17 (O2)
unnamed: C8.2, J7.1, R21.2, U2.16 (O3)
unnamed: C9.2, J8.1, R22.2, U2.15 (O4)
unnamed: C10.2, J9.1, R23.2, U2.14 (O5)
unnamed: C15.2, J14.1, R26.2, U2.11 (O8)
unnamed: C16.2, J17.1, R29.2, U3.16 (O3)
unnamed: C17.2, J22.1, R34.2, U3.11 (O8)
unnamed: C18.2, J15.1, R27.2, U3.18 (O1)
unnamed: C19.2, J16.1, R28.2, U3.17 (O2)
unnamed: C20.2, J18.1, R30.2, U3.15 (O4)
unnamed: C21.2, J20.1, R32.2, U3.13 (O6)
unnamed: C22.2, J21.1, R33.2, U3.12 (O7)
unnamed: C23.2, J19.1, R31.2, U3.14 (O5)
unnamed: C111.2, J13.1
unnamed: C112.2, J12.1
unnamed: DA0.1 (K), R26.1
unnamed: DA1.1 (K), R25.1
unnamed: DA2.1 (K), R24.1
unnamed: DA3.1 (K), R23.1
unnamed: DA4.1 (K), R22.1
unnamed: DA5.1 (K), R21.1
unnamed: DA6.1 (K), R20.1
unnamed: DA7.1 (K), R19.1
unnamed: DB0.1 (K), R34.1
unnamed: DB1.1 (K), R33.1
unnamed: DB2.1 (K), R32.1
unnamed: DB3.1 (K), R31.1
unnamed: DB4.1 (K), R30.1
unnamed: DB5.1 (K), R29.1
unnamed: DB6.1 (K), R28.1
unnamed: DB7.1 (K), R27.1
unnamed: JP1.2, U1.15 (A0)
unnamed: JP2.2, U1.16 (A1)
unnamed: JP4.2, U1.17 (A2)
unnamed: R3.1, U4.1
unnamed: R3.2, U1.28 (GPA7)
unnamed: R4.1, U5.1
unnamed: R4.2, U1.27 (GPA6)
unnamed: R5.1, U6.1
unnamed: R5.2, U1.26 (GPA5)
unnamed: R6.1, U7.1
unnamed: R6.2, U1.25 (GPA4)
unnamed: R7.1, U8.1
unnamed: R7.2, U1.24 (GPA3)
unnamed: R8.1, U9.1
unnamed: R8.2, U1.23 (GPA2)
unnamed: R9.1, U10.1
unnamed: R9.2, U1.22 (GPA1)
unnamed: R10.1, U11.1
unnamed: R10.2, U1.21 (GPA0)
unnamed: R11.1, U12.1
unnamed: R11.2, U1.8 (GPB7)
unnamed: R12.1, U13.1
unnamed: R12.2, U1.7 (GPB6)
unnamed: R13.1, U14.1
unnamed: R13.2, U1.6 (GPB5)
unnamed: R14.1, U15.1
unnamed: R14.2, U1.5 (GPB4)
unnamed: R15.1, U16.1
unnamed: R15.2, U1.4 (GPB3)
unnamed: R16.1, U17.1
unnamed: R16.2, U1.3 (GPB2)
unnamed: R17.1, U18.1
unnamed: R17.2, U1.2 (GPB1)
unnamed: R18.1, U19.1
unnamed: R18.2, U1.1 (GPB0)
unnamed: U2.1 (I1), U4.3
unnamed: U2.2 (I2), U5.3
unnamed: U2.3 (I3), U6.3
unnamed: U2.4 (I4), U7.3
unnamed: U2.5 (I5), U8.3
unnamed: U2.6 (I6), U9.3
unnamed: U2.7 (I7), U10.3
unnamed: U2.8 (I8), U11.3
unnamed: U3.1 (I1), U12.3
unnamed: U3.2 (I2), U13.3
unnamed: U3.3 (I3), U14.3
unnamed: U3.4 (I4), U15.3
unnamed: U3.5 (I5), U16.3
unnamed: U3.6 (I6), U17.3
unnamed: U3.7 (I7), U18.3
unnamed: U3.8 (I8), U19.3
RLYGND: C107.1, L17.2, U2.9 (GND), U3.9 (GND)
RLYPWR: C2.1, C3.1, C4.1, C5.1, C6.1, C7.1, C8.1, C9.1, C10.1, C15.1, C16.1, C17.1, C18.1, C19.1, C20.1, C21.1, C22.1, C23.1, C107.2, C111.1, DA0.2 (A), DA1.2 (A), DA2.2 (A), DA3.2 (A), DA4.2 (A), DA5.2 (A), DA6.2 (A), DA7.2 (A), DB0.2 (A), DB1.2 (A), DB2.2 (A), DB3.2 (A), DB4.2 (A), DB5.2 (A), DB6.2 (A), DB7.2 (A), J5.2, J6.2, J7.2, J8.2, J9.2, J10.2, J11.2, J14.2, J15.2, J16.2, J17.2, J18.2, J19.2, J20.2, J21.2, J22.2, L18.1, U2.10 (COM), U3.10 (COM), U4.4, U5.4, U6.4, U7.4, U8.4, U9.4, U10.4, U11.4, U12.4, U13.4, U14.4, U15.4, U16.4, U17.4, U18.4, U19.4
SCL: J1.3, R1.2, U1.12 (SCL)
SDA: J1.7, R2.2, U1.13 (SDA)
SELPWR: C11.1, C73.2, JP3.2, JP6.2

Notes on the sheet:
Optoisolated Relay Control Board by Daniel Marks KW4TI
April 12, 2019 version
